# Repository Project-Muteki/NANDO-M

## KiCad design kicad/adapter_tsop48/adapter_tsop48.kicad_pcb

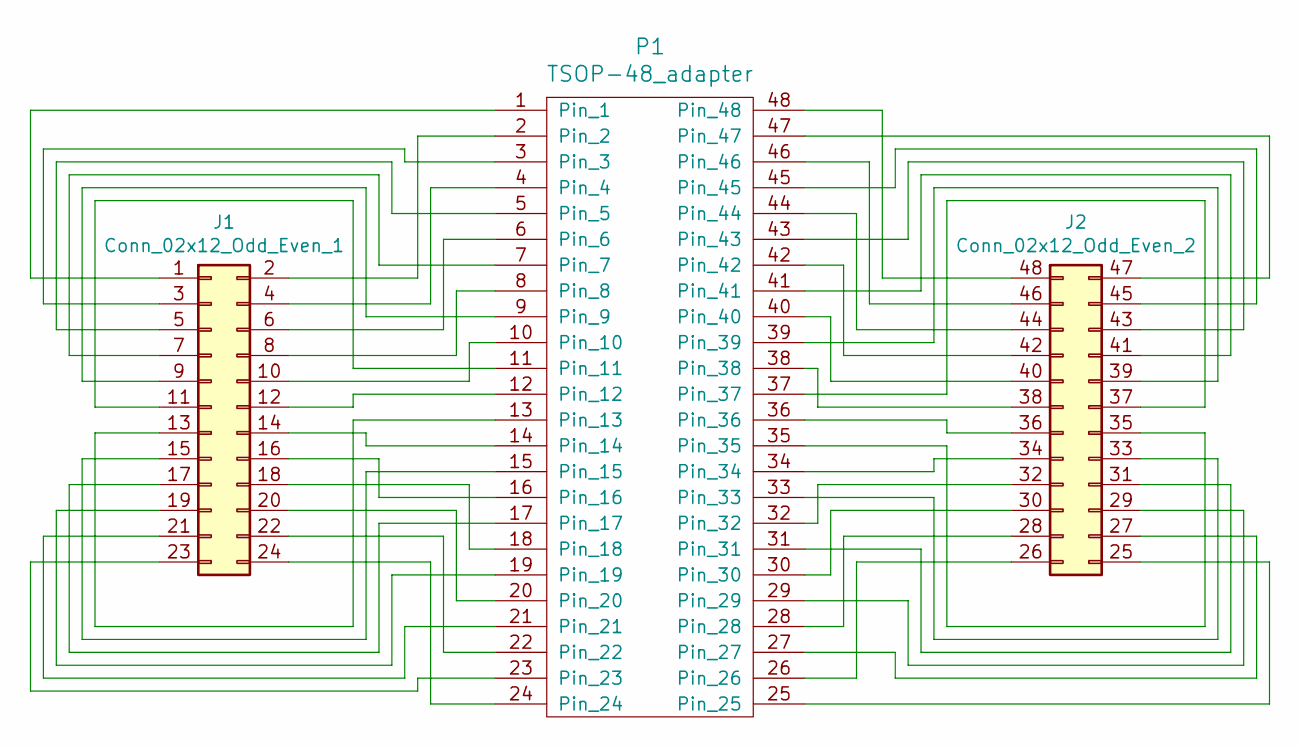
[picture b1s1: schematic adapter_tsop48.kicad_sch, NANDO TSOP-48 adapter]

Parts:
J1: Conn_02x12_Odd_Even_1; PinSocket_2x12_P2.54mm_Vertical
J2: Conn_02x12_Odd_Even_2; PinSocket_2x12_P2.54mm_Vertical_2
P1: TSOP-48_adapter; TSOP-48

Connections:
unnamed: J1.1, P1.1
unnamed: J1.2, P1.2
unnamed: J1.3, P1.3
unnamed: J1.4, P1.4
unnamed: J1.5, P1.5
unnamed: J1.6, P1.6
unnamed: J1.7, P1.7
unnamed: J1.8, P1.8
unnamed: J1.9, P1.9
unnamed: J1.10, P1.10
unnamed: J1.11, P1.11
unnamed: J1.12, P1.12
unnamed: J1.13, P1.13
unnamed: J1.14, P1.14
unnamed: J1.15, P1.15
unnamed: J1.16, P1.16
unnamed: J1.17, P1.17
unnamed: J1.18, P1.18
unnamed: J1.19, P1.19
unnamed: J1.20, P1.20
unnamed: J1.21, P1.21
unnamed: J1.22, P1.22
unnamed: J1.23, P1.23
unnamed: J1.24, P1.24
unnamed: J2.25, P1.25
unnamed: J2.26, P1.26
unnamed: J2.27, P1.27
unnamed: J2.28, P1.28
unnamed: J2.29, P1.29
unnamed: J2.30, P1.30
unnamed: J2.31, P1.31
unnamed: J2.32, P1.32
unnamed: J2.33, P1.33
unnamed: J2.34, P1.34
unnamed: J2.35, P1.35
unnamed: J2.36, P1.36
unnamed: J2.37, P1.37
unnamed: J2.38, P1.38
unnamed: J2.39, P1.39
unnamed: J2.40, P1.40
unnamed: J2.41, P1.41
unnamed: J2.42, P1.42
unnamed: J2.43, P1.43
unnamed: J2.44, P1.44
unnamed: J2.45, P1.45
unnamed: J2.46, P1.46
unnamed: J2.47, P1.47
unnamed: J2.48, P1.48

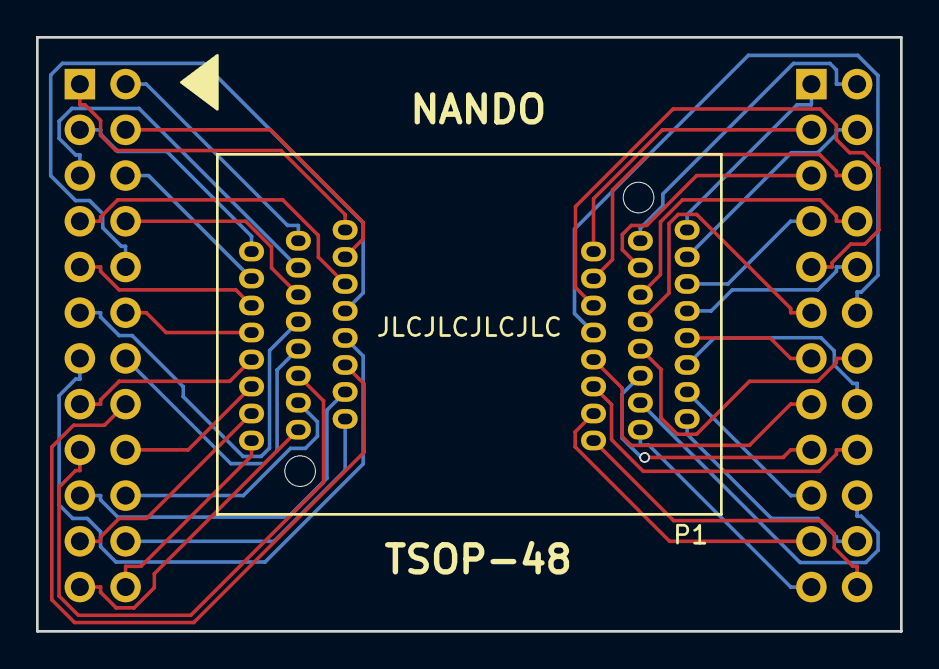
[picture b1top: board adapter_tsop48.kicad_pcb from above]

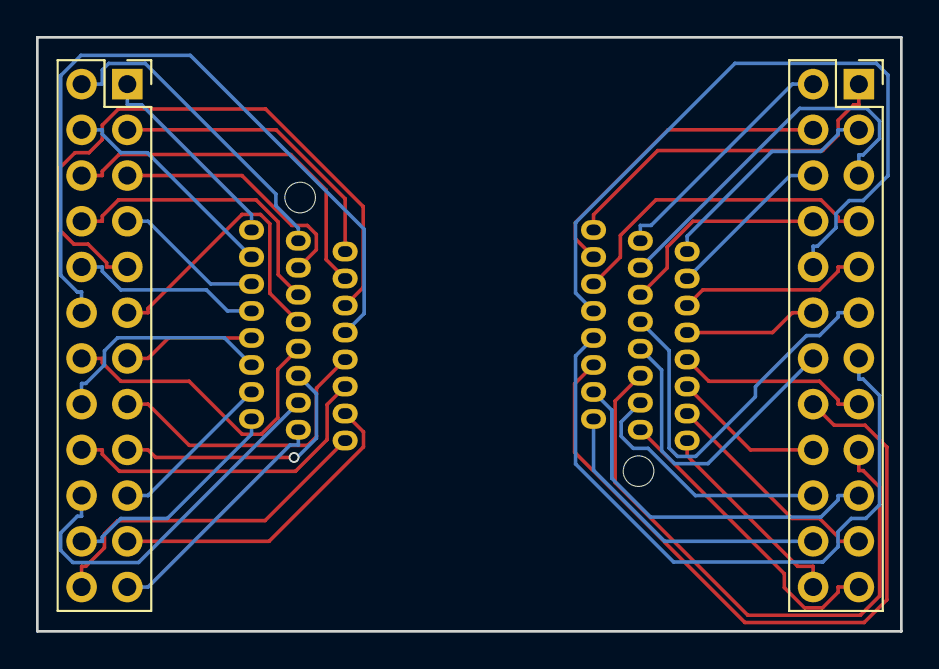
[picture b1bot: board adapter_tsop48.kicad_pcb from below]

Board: 2 copper layers, 48.0 x 33.0 mm, 3 parts (2 on the bottom side), 48 nets.

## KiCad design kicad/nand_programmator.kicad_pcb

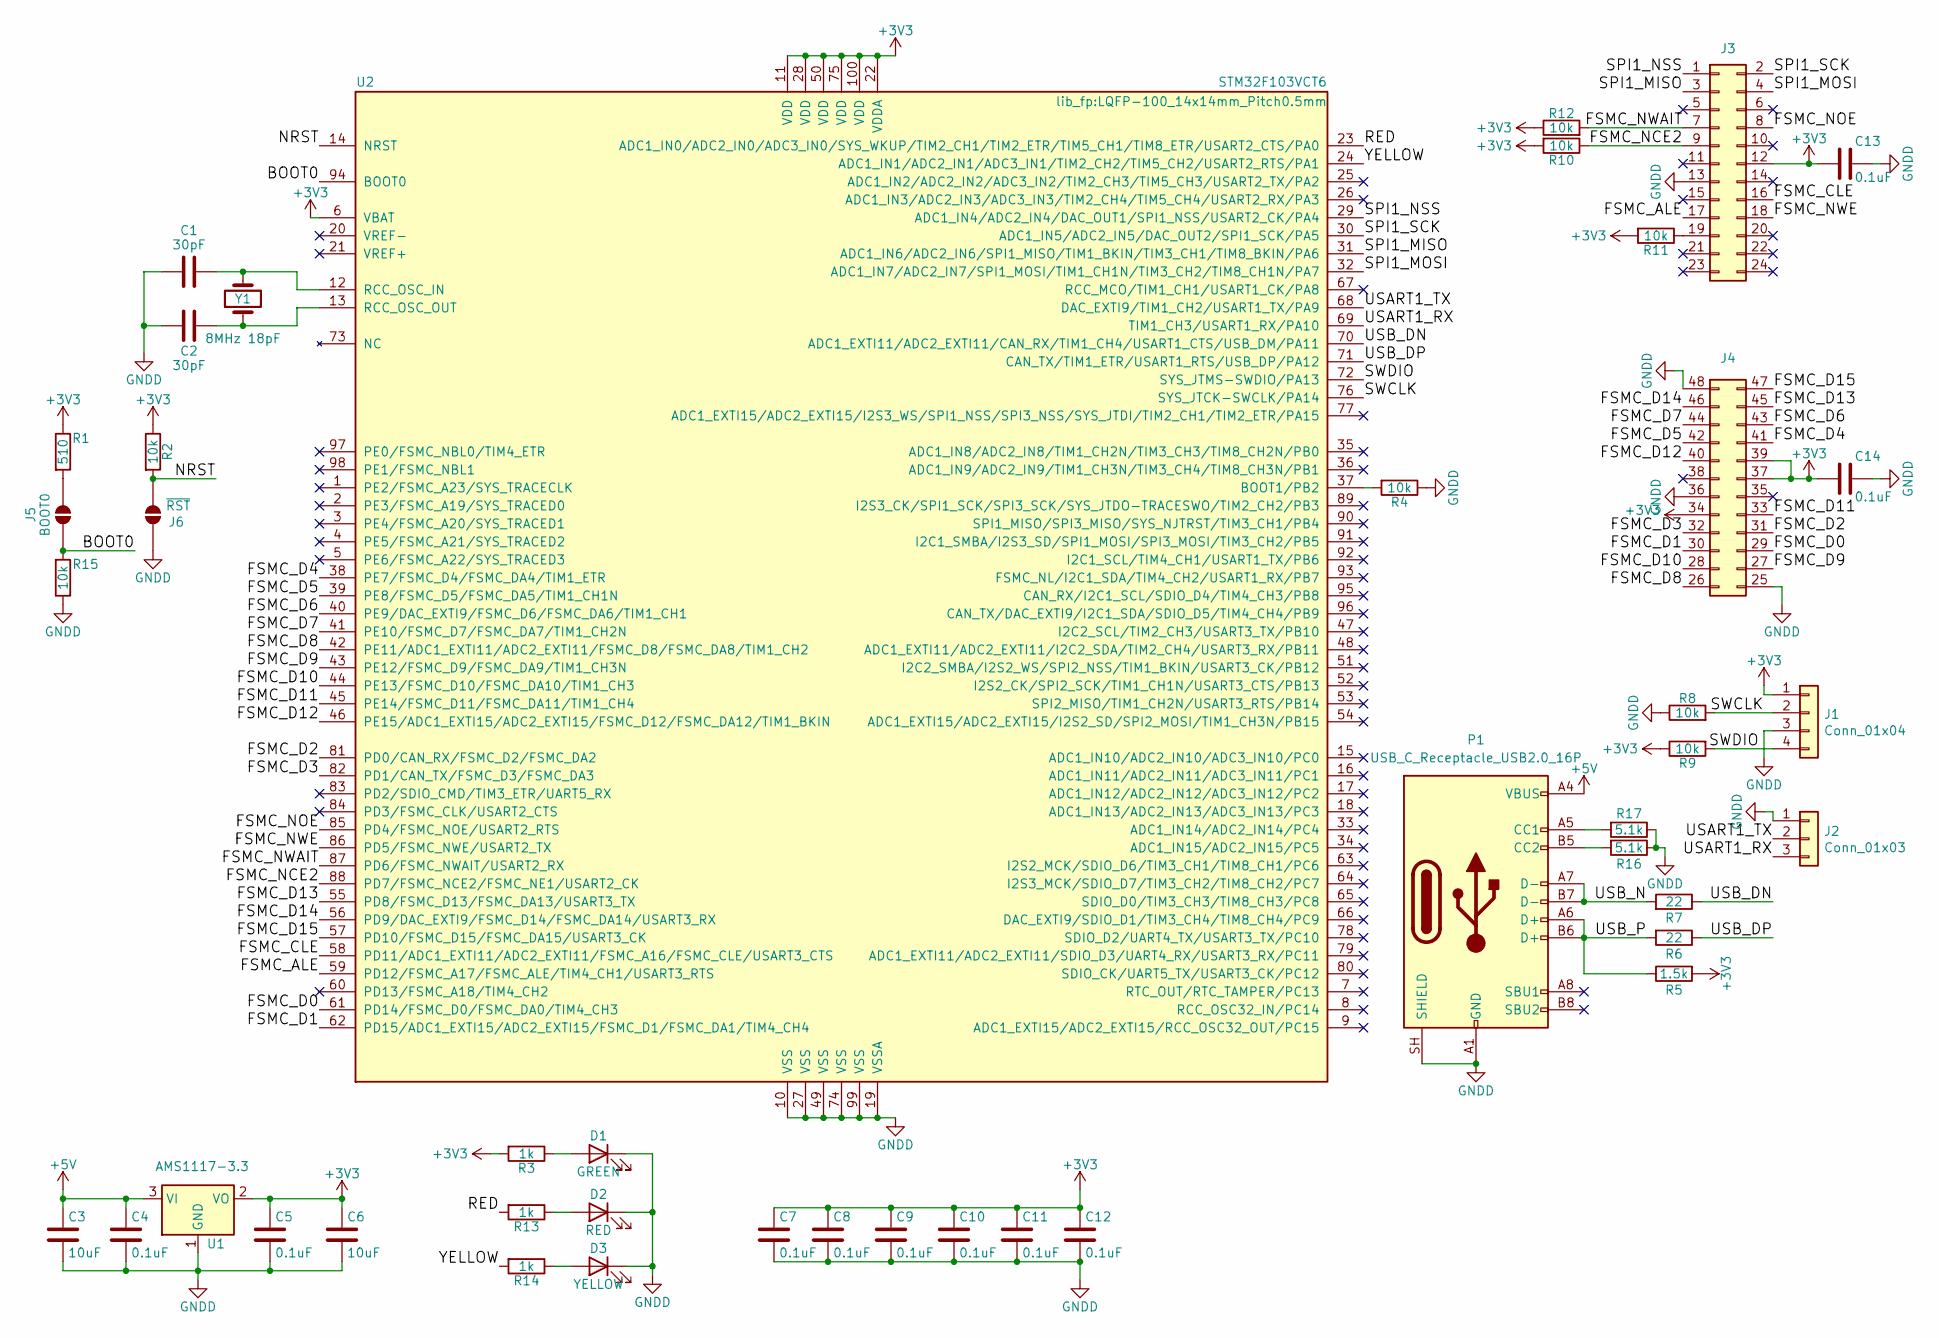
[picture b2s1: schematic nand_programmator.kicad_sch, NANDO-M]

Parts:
C1, C2: 30pF; C_0805_2012Metric_Pad1.15x1.40mm_HandSolder; Farnell Ref 2905258
C3, C6: 10uF; C_0805_2012Metric_Pad1.15x1.40mm_HandSolder; Farnell Ref 2112850
C4, C5, C7, C8, C9, C10, C11, C12, C13, C14: 0.1uF; C_0805_2012Metric_Pad1.15x1.40mm_HandSolder; Farnell Ref 2320839
D1: GREEN; LED_0805_2012Metric_Pad1.15x1.40mm_HandSolder; Farnell Ref 2099239
D2: RED; LED_0805_2012Metric_Pad1.15x1.40mm_HandSolder; Farnell Ref 2099236
D3: YELLOW; LED_0805_2012Metric_Pad1.15x1.40mm_HandSolder; Farnell Ref 2099243
J1: Conn_01x04; PinHeader_1x04_P2.54mm_Vertical; Farnell Ref 3049529
J2: Conn_01x03; PinHeader_1x03_P2.54mm_Vertical; Farnell Ref 3049527
J3: Conn_02x12_Odd_Even_Left; PinHeader_2x12_P2.54mm_Vertical; Farnell Ref 3049468
J4: Conn_02x12_Odd_Even_Right; PinHeader_2x12_P2.54mm_Vertical_2; Farnell Ref 3049468
J5: BOOT0; SolderJumper-2_P1.3mm_Open_RoundedPad1.0x1.5mm
J6: ~{RST}; SolderJumper-2_P1.3mm_Open_RoundedPad1.0x1.5mm
P1: USB_C_Receptacle_USB2.0_16P; USB_C_Receptacle_GCT_USB4105-xx-A_16P_TopMnt_Horizontal
R1: 510; R_0805_2012Metric_Pad1.15x1.40mm_HandSolder; Farnell Ref 2447679
R2, R4, R8, R9, R10, R11, R12, R15: 10k; R_0805_2012Metric_Pad1.15x1.40mm_HandSolder; Farnell Ref 2447553
R3, R13, R14: 1k; R_0805_2012Metric_Pad1.15x1.40mm_HandSolder; Farnell Ref 2447587
R5: 1.5k; R_0805_2012Metric_Pad1.15x1.40mm_HandSolder; Farnell Ref 2447592
R6, R7: 22; R_0805_2012Metric_Pad1.15x1.40mm_HandSolder; Farnell Ref 2447609
R16, R17: 5.1k; R_0805_2012Metric_Pad1.15x1.40mm_HandSolder
U1: AMS1117-3.3; SOT-223-3_TabPin2; Farnell Ref 3007498
U2: STM32F103VCT6; LQFP-100_14x14mm_Pitch0.5mm; Farnell Ref 1624139
Y1: 8MHz 18pF; Crystal_SMD_HC49-SD; Farnell Ref 2393160

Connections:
+3V3: C5.1, C6.1, C7.1, C8.1, C9.1, C10.1, C11.1, C12.1, C13.2, C14.2, J1.1, J3.12, J4.34, J4.37, J4.39, R1.1, R2.1, R3.2, R5.2, R9.1, R10.2, R11.2, R12.1, U1.2 (VO), U2.6 (VBAT), U2.11 (VDD), U2.22 (VDDA), U2.28 (VDD), U2.50 (VDD), U2.75 (VDD), U2.100 (VDD)
+5V: C3.1, C4.1, P1.A4 (VBUS), P1.A9 (VBUS), P1.B4 (VBUS), P1.B9 (VBUS), U1.3 (VI)
/BOOT0: J5.1 (A), R15.2, U2.94 (BOOT0)
/FSMC_ALE: J3.17, U2.59 (PD12/FSMC_A17/FSMC_ALE/TIM4_CH1/USART3_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)
/FSMC_CLE: J3.16, U2.58 (PD11/ADC1_EXTI11/ADC2_EXTI11/FSMC_A16/F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)
/FSMC_D0: J4.29, U2.61 (PD14/FSMC_D0/FSMC_DA0/TIM4_CH3)
/FSMC_D1: J4.30, U2.62 (PD15/ADC1_EXTI15/ADC2_EXTI15/FSMC_D1/FS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)
/FSMC_D2: J4.31, U2.81 (PD0/CAN_RX/FSMC_D2/FSMC_DA2)
/FSMC_D3: J4.32, U2.82 (PD1/CAN_TX/FSMC_D3/FSMC_DA3)
/FSMC_D4: J4.41, U2.38 (PE7/FSMC_D4/FSMC_DA4/TIM1_ETR)
/FSMC_D5: J4.42, U2.39 (PE8/FSMC_D5/FSMC_DA5/TIM1_CH1N)
/FSMC_D6: J4.43, U2.40 (PE9/DAC_EXTI9/FSMC_D6/FSMC_DA6/TIM1_CH1)
/FSMC_D7: J4.44, U2.41 (PE10/FSMC_D7/FSMC_DA7/TIM1_CH2N)
/FSMC_D8: J4.26, U2.42 (PE11/ADC1_EXTI11/ADC2_EXTI11/FSMC_D8/FS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)
/FSMC_D9: J4.27, U2.43 (PE12/FSMC_D9/FSMC_DA9/TIM1_CH3N)
/FSMC_D10: J4.28, U2.44 (PE13/FSMC_D10/FSMC_DA10/TIM1_CH3)
/FSMC_D11: J4.33, U2.45 (PE14/FSMC_D11/FSMC_DA11/TIM1_CH4)
/FSMC_D12: J4.40, U2.46 (PE15/ADC1_EXTI15/ADC2_EXTI15/FSMC_D12/F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)
/FSMC_D13: J4.45, U2.55 (PD8/FSMC_D13/FSMC_DA13/USART3_TX)
/FSMC_D14: J4.46, U2.56 (PD9/DAC_EXTI9/FSMC_D14/FSMC_DA14/USART3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)
/FSMC_D15: J4.47, U2.57 (PD10/FSMC_D15/FSMC_DA15/USART3_CK)
/FSMC_NCE2: J3.9, R10.1, U2.88 (PD7/FSMC_NCE2/FSMC_NE1/USART2_CK)
/FSMC_NOE: J3.8, U2.85 (PD4/FSMC_NOE/USART2_RTS)
/FSMC_NWAIT: J3.7, R12.2, U2.87 (PD6/FSMC_NWAIT/USART2_RX)
/FSMC_NWE: J3.18, U2.86 (PD5/FSMC_NWE/USART2_TX)
/NRST: J6.2 (B), R2.2, U2.14 (NRST)
/RED: R13.2, U2.23 (ADC1_IN0/ADC2_IN0/ADC3_IN0/SYS_WKUP/TIM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)
/SPI1_MISO: J3.3, U2.31 (ADC1_IN6/ADC2_IN6/SPI1_MISO/TIM1_BKIN/T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)
/SPI1_MOSI: J3.4, U2.32 (ADC1_IN7/ADC2_IN7/SPI1_MOSI/TIM1_CH1N/T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)
/SPI1_NSS: J3.1, U2.29 (ADC1_IN4/ADC2_IN4/DAC_OUT1/SPI1_NSS/USA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)
/SPI1_SCK: J3.2, U2.30 (ADC1_IN5/ADC2_IN5/DAC_OUT2/SPI1_SCK/PA5)
/SWCLK: J1.2, R8.2, U2.76 (SYS_JTCK-SWCLK/PA14)
/SWDIO: J1.4, R9.2, U2.72 (SYS_JTMS-SWDIO/PA13)
/USART1_RX: J2.3, U2.69 (TIM1_CH3/USART1_RX/PA10)
/USART1_TX: J2.2, U2.68 (DAC_EXTI9/TIM1_CH2/USART1_TX/PA9)
/USB_DN: R7.1, U2.70 (ADC1_EXTI11/ADC2_EXTI11/CAN_RX/TIM1_CH4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)
/USB_DP: R6.1, U2.71 (CAN_TX/TIM1_ETR/USART1_RTS/USB_DP/PA12)
/USB_N: P1.A7 (D-), P1.B7 (D-), R7.2
/USB_P: P1.A6 (D+), P1.B6 (D+), R5.1, R6.2
/YELLOW: R14.2, U2.24 (ADC1_IN1/ADC2_IN1/ADC3_IN1/TIM2_CH2/TIM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)
GNDD: C1.2, C2.2, C3.2, C4.2, C5.2, C6.2, C7.2, C8.2, C9.2, C10.2, C11.2, C12.2, C13.1, C14.1, D1.1 (K), D2.1 (K), D3.1 (K), J1.3, J2.1, J3.13, J4.25, J4.36, J4.48, J6.1 (A), P1.A1 (GND), P1.A12 (GND), P1.B1 (GND), P1.B12 (GND), P1.SH (SHIELD), R4.1, R8.1, R15.1, R16.1, R17.1, U1.1 (GND), U2.10 (VSS), U2.19 (VSSA), U2.27 (VSS), U2.49 (VSS), U2.74 (VSS), U2.99 (VSS)
unnamed: D1.2 (A), R3.1
unnamed: D2.2 (A), R13.1
unnamed: D3.2 (A), R14.1
unnamed: J3.19, R11.1
unnamed: J5.2 (B), R1.2
unnamed: P1.A5 (CC1), R17.2
unnamed: P1.B5 (CC2), R16.2
unnamed: R4.2, U2.37 (BOOT1/PB2)
unnamed: C1.1, U2.12 (RCC_OSC_IN), Y1.2
unnamed: C2.1, U2.13 (RCC_OSC_OUT), Y1.1

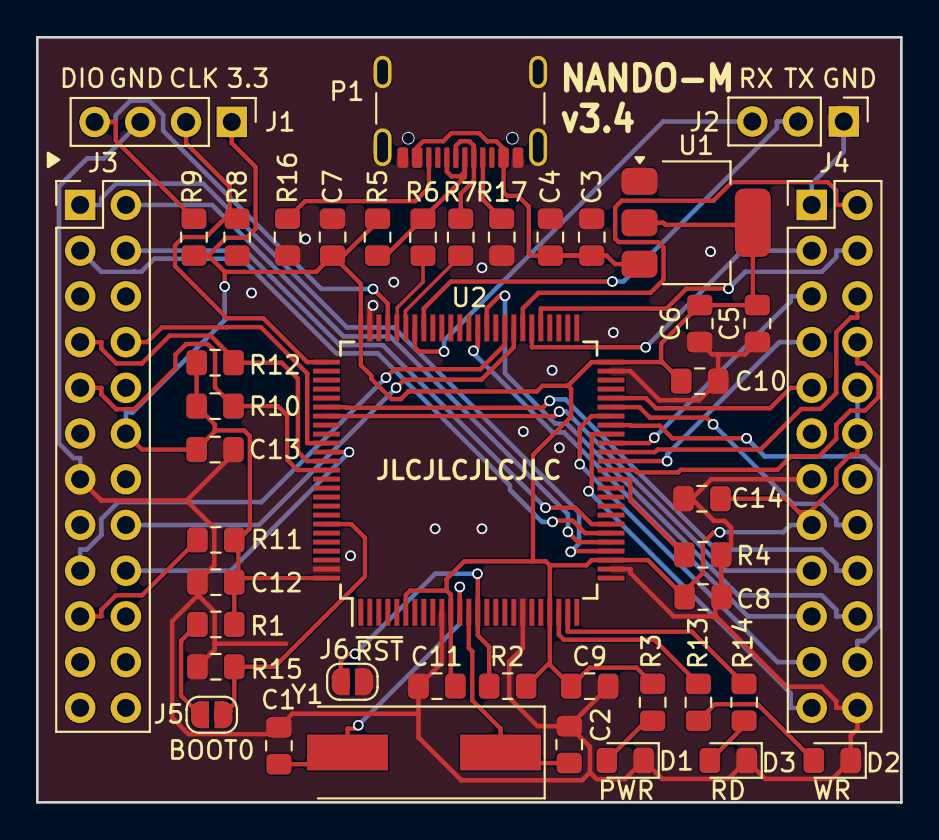
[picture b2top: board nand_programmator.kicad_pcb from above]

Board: 2 copper layers, 48.0 x 42.5 mm, 44 parts (0 on the bottom side), 51 nets.
